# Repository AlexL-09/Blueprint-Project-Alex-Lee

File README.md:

# Blueprint-Project-Alex-Lee

Project overview and description:
I was new to most of these programs so it took a while to learn, but after starting my 3rd iteration, I got somewhat used to all the features and was able to finish this project.
I made this macropad to control music. It has mute button, volume up, volume down, previous track, pause, and next track buttons. I had a lot of fun making this although I did occasionally leave it for a few weeks when things got tough. Ultimately, I didn't give up and somehow it works correctly.

Inspiration: I wanted to learn how to design my own pcb, while also making a very basic alternative to my elgato stream deck that sadly broke recently.

Features (very basic):  
6 keys<br>
thats it (I guess I had countersink for screws)

BOM:  
1x XIAO RP2040  
6x Cherry MX Switches  
6x Blank Keycaps  
4x M3x16 Bolt  
4x M3 Heatset Inserts  

Schematic (Kicad) :

PCB (Kicad) :

CAD images (Fusion 360):
assembled:

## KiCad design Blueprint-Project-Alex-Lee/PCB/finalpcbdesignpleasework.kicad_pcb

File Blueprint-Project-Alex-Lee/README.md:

# Blueprint-Project-Alex-Lee
Repository for project files

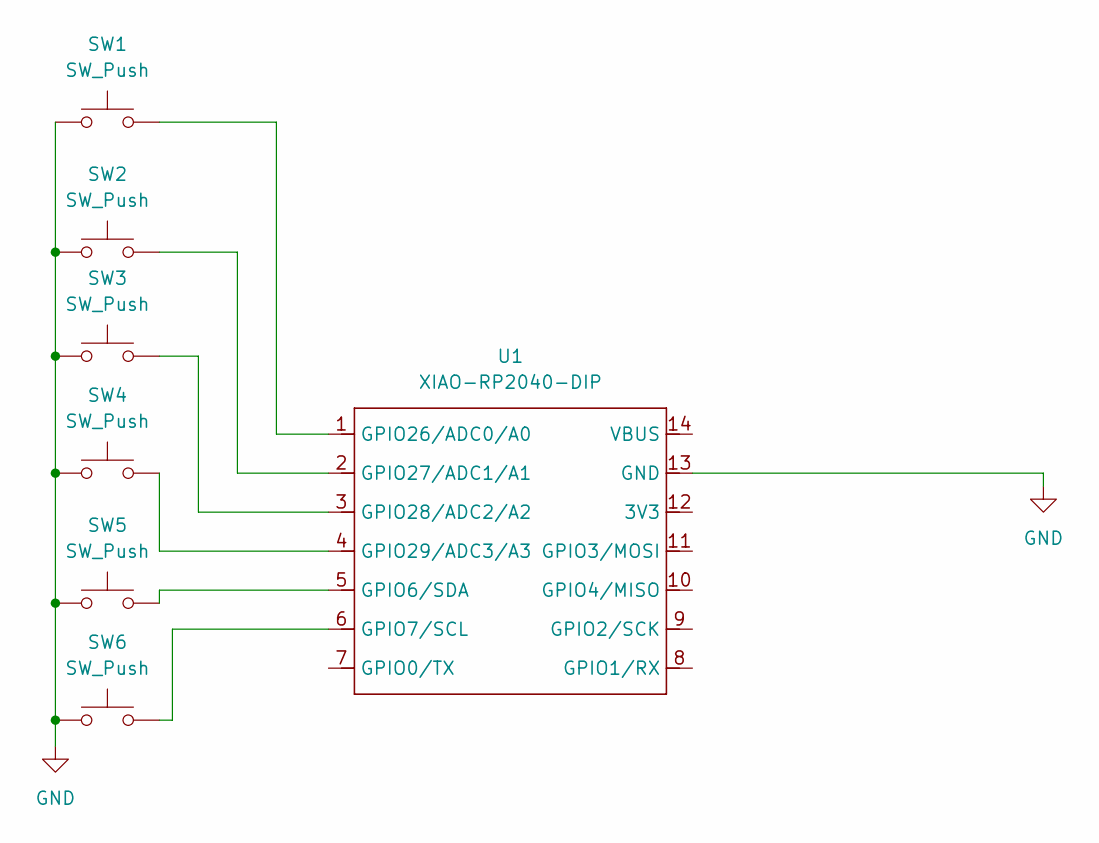
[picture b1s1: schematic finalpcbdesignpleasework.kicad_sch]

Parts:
SW1, SW2, SW3, SW4, SW5, SW6: SW_Push; SW_Cherry_MX_1.00u_PCB
U1: XIAO-RP2040-DIP

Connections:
GND: SW1.1, SW2.1, SW3.1, SW4.1, SW5.1, SW6.1, U1.13 (GND)
unnamed: SW5.2, U1.5 (GPIO6/SDA)
unnamed: SW6.2, U1.6 (GPIO7/SCL)
unnamed: SW1.2, U1.1 (GPIO26/ADC0/A0)
unnamed: SW2.2, U1.2 (GPIO27/ADC1/A1)
unnamed: SW3.2, U1.3 (GPIO28/ADC2/A2)
unnamed: SW4.2, U1.4 (GPIO29/ADC3/A3)

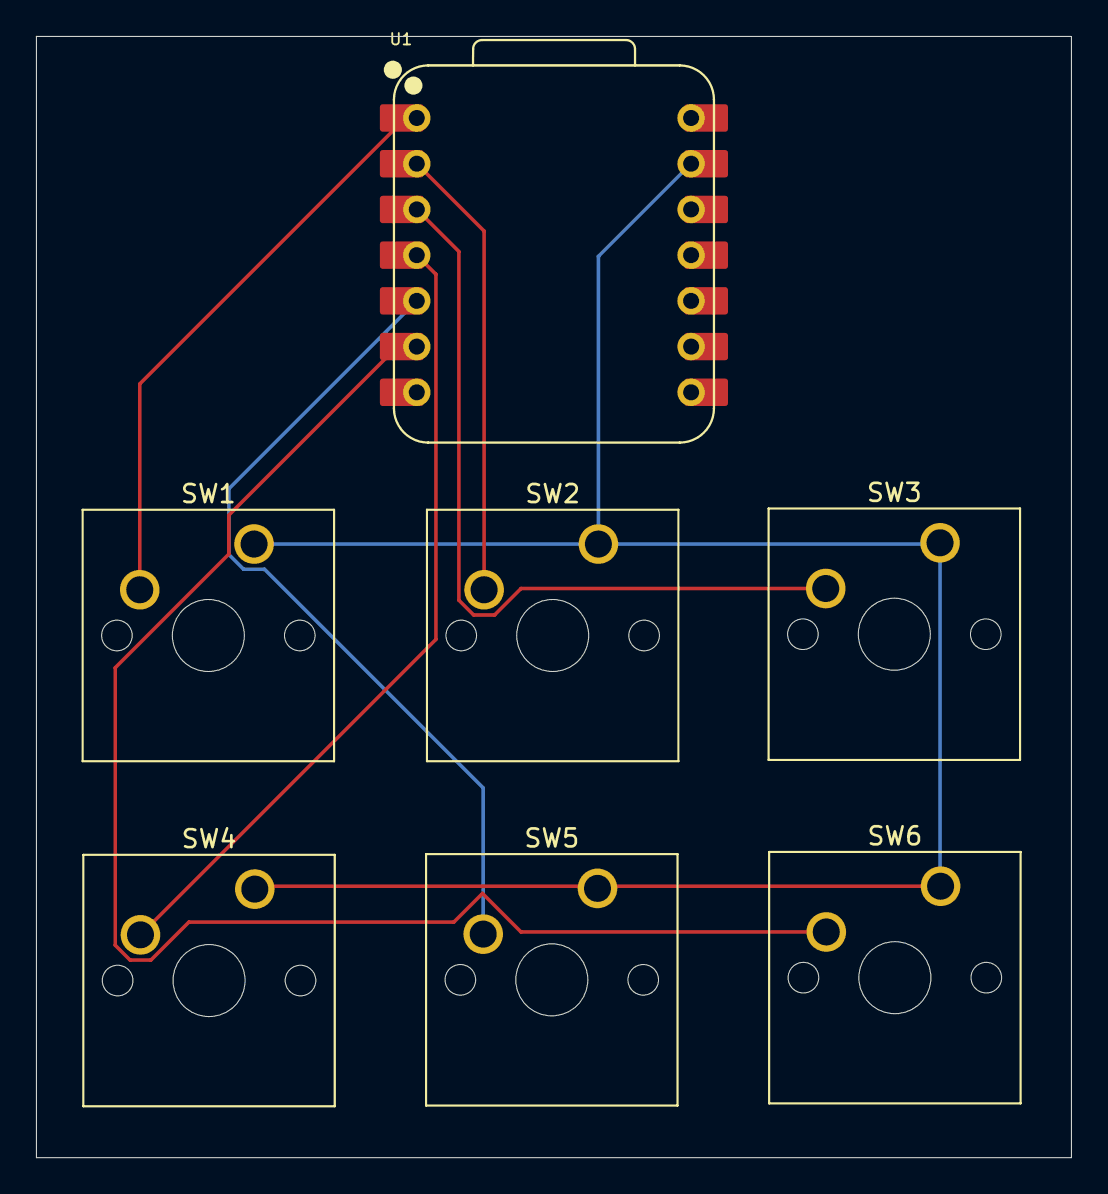
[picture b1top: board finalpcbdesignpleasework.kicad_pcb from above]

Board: 2 copper layers, 57.5 x 62.3 mm, 7 parts (0 on the bottom side), 7 nets.

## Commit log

2026-03-07 Rename Screenshot 2026-03-06 230536.png to PCB screenshot
2026-03-07 Rename Screenshot 2026-03-06 230520.png to Schematic Screenshot
2026-03-07 Rename Screenshot 2026-03-07 100302.png to full cad model with keycaps
2026-03-07 Rename Screenshot 2026-03-07 100355.png to full cad model open
2026-03-07 Rename full cad model open to full cad model open screenshot
2026-03-07 Rename full cad model with keycaps to full cad model with keycaps screenshot
2026-03-07 Rename full cad model open screenshot to full cad model open
2026-03-07 Rename Screenshot 2026-03-07 100355.png to caseopenmodel.png
2026-03-07 Rename Screenshot 2026-03-07 100302.png to fullcadmodel.png
2026-03-07 Rename PCB screenshot to pcb.png
2026-03-07 Rename Schematic Screenshot to Schematic.png
2026-03-13 Rename PCB CASE FINAL VERSION.f3d to PCB SOURCE FILES.f3d
2026-03-13 Rename Screenshot 2026-03-12 200855.png to fullcadmodel.png
2026-03-13 Rename Screenshot 2026-03-12 201538.png to pcb.png
